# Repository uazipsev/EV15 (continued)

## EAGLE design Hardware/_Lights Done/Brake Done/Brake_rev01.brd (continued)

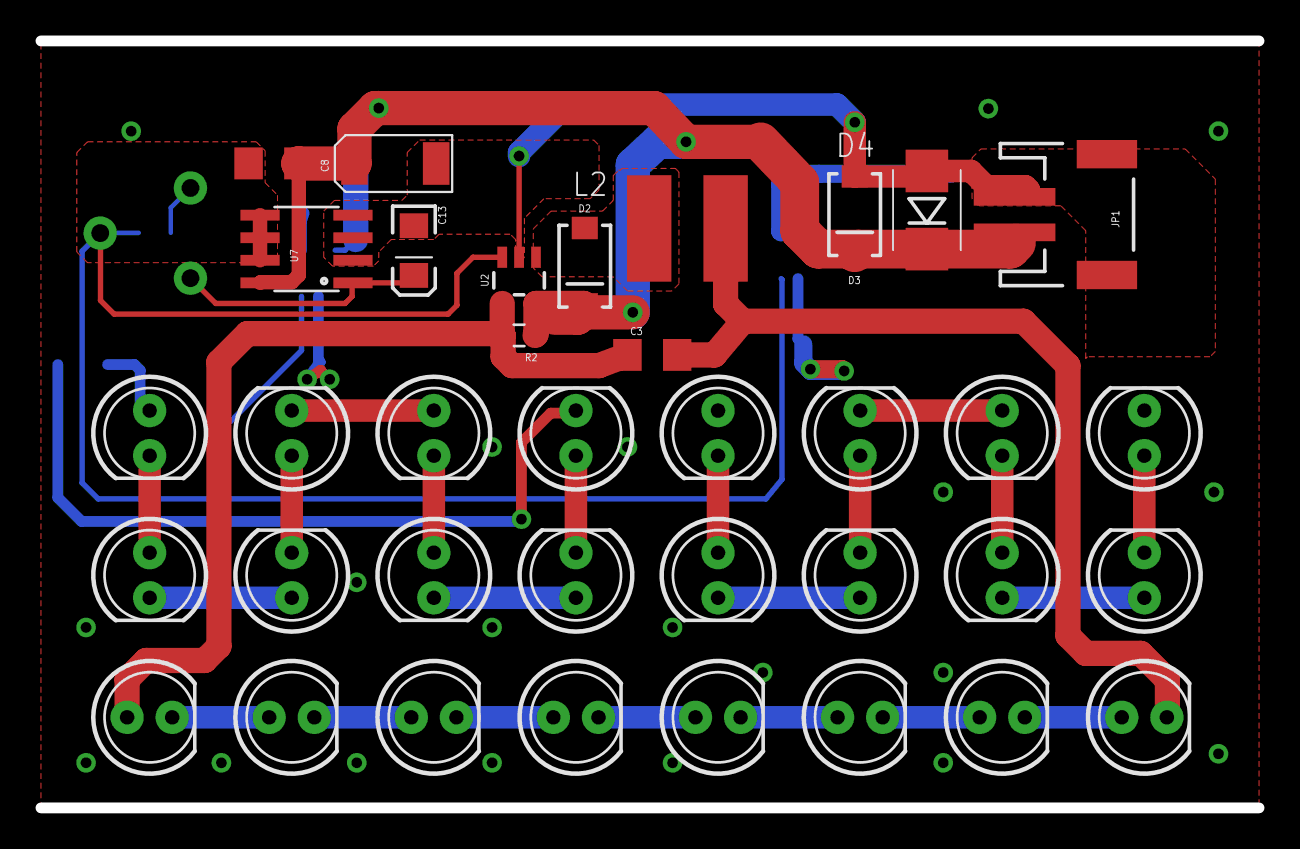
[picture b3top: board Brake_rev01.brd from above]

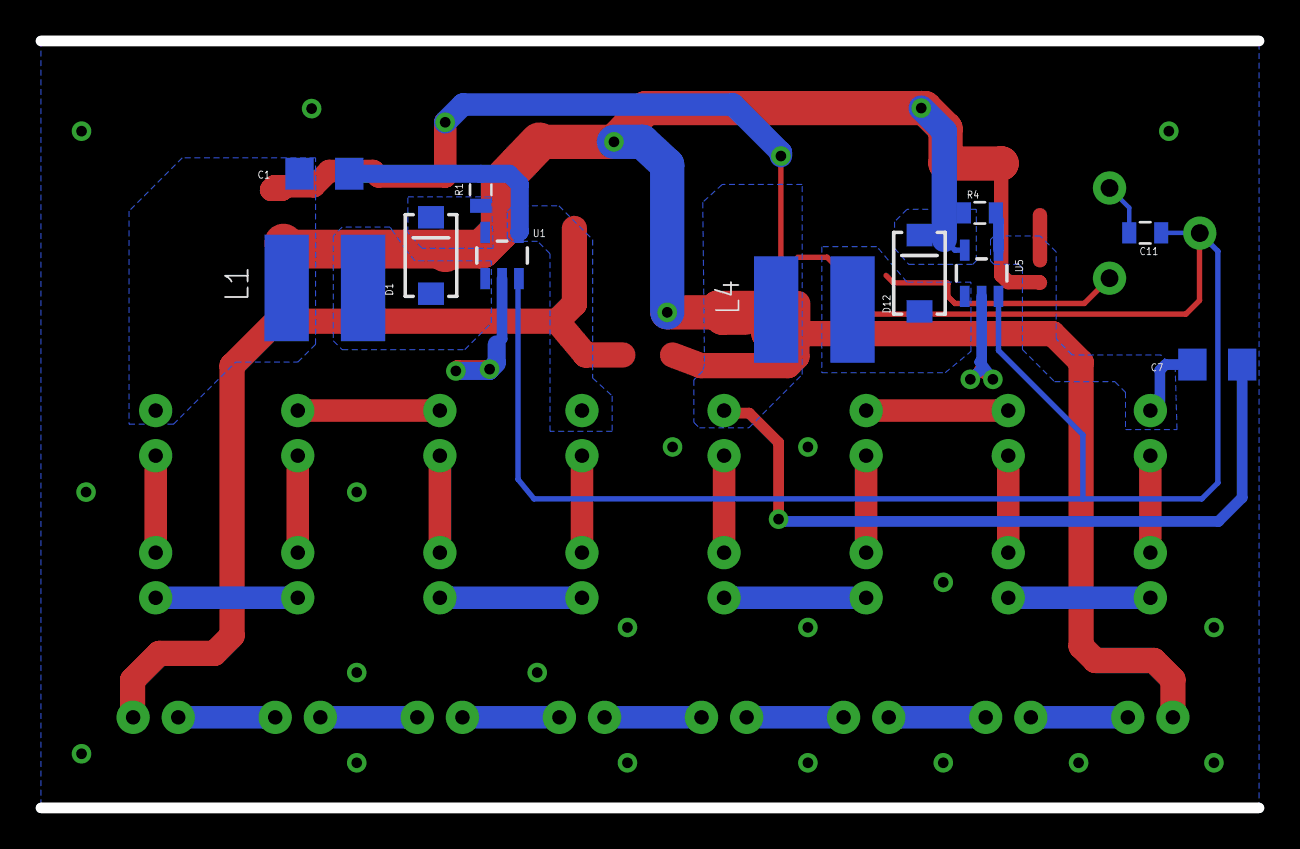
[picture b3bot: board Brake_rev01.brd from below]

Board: 2 copper layers, 68.6 x 43.2 mm, 50 parts (11 on the bottom side), 34 nets.

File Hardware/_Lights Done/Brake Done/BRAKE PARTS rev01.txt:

Partlist

Exported from Brake_rev01.sch at 1/12/15 3:03 PM

EAGLE Version 6.5.0 Copyright (c) 1988-2013 CadSoft

Assembly variant: 

Part     Value           Device                 Package   Library                    Sheet

C1       1uF             1.0UF50V10%(1206)      1206      SparkFun-Capacitors        1
C3       1uF             1.0UF50V10%(1206)      1206      SparkFun-Capacitors        1
C7       1uF             1.0UF50V10%(1206)      1206      SparkFun-Capacitors        1
C8       2.2uF           2.2UF50V10%(1206)      1206      SparkFun-Capacitors        1
C11      10uF            CAP0805                0805      SparkFun-Capacitors        1
C12                      CAP_POL6032            EIA6032   SparkFun-Capacitors        1
C13                      CAP_POL1206            EIA3216   SparkFun-Capacitors        1
D1       MBRA140         DIODE-SCHOTTKY-MBRA140 SMA-DIODE SparkFun-DiscreteSemi      1
D2       MBRA140         DIODE-SCHOTTKY-MBRA140 SMA-DIODE SparkFun-DiscreteSemi      1
D3       TVS             TVS                    SMA-DIODE SparkFun-DiscreteSemi      1
D4       30v             DIODE-ZENERSMB         SMB-DIODE SparkFun-DiscreteSemi      1
D12      MBRA140         DIODE-SCHOTTKY-MBRA140 SMA-DIODE SparkFun-DiscreteSemi      1
JP1      M02-JST-2MM-SMT M02-JST-2MM-SMT        JST-2-SMD SparkFun-Connectors        1
L1       33uH            INDUCTORBOURNS_SRN6045 SRN6045   SparkFun-Passives          1
L2       33uH            INDUCTORBOURNS_SRN6045 SRN6045   SparkFun-Passives          1
L4       33uH            INDUCTORBOURNS_SRN6045 SRN6045   SparkFun-Passives          1
LED1                     LED5MM                 LED5MM    SparkFun-LED               1
LED2                     LED5MM                 LED5MM    SparkFun-LED               1
LED3                     LED5MM                 LED5MM    SparkFun-LED               1
LED4                     LED5MM                 LED5MM    SparkFun-LED               1
LED5                     LED5MM                 LED5MM    SparkFun-LED               1
LED6                     LED5MM                 LED5MM    SparkFun-LED               1
LED7                     LED5MM                 LED5MM    SparkFun-LED               1
LED8                     LED5MM                 LED5MM    SparkFun-LED               1
LED9                     LED5MM                 LED5MM    SparkFun-LED               1
LED10                    LED5MM                 LED5MM    SparkFun-LED               1
LED11                    LED5MM                 LED5MM    SparkFun-LED               1
LED12                    LED5MM                 LED5MM    SparkFun-LED               1
LED13                    LED5MM                 LED5MM    SparkFun-LED               1
LED14                    LED5MM                 LED5MM    SparkFun-LED               1
LED15                    LED5MM                 LED5MM    SparkFun-LED               1
LED16                    LED5MM                 LED5MM    SparkFun-LED               1
LED17                    LED5MM                 LED5MM    SparkFun-LED               1
LED18                    LED5MM                 LED5MM    SparkFun-LED               1
LED19                    LED5MM                 LED5MM    SparkFun-LED               1
LED20                    LED5MM                 LED5MM    SparkFun-LED               1
LED21                    LED5MM                 LED5MM    SparkFun-LED               1
LED22                    LED5MM                 LED5MM    SparkFun-LED               1
LED23                    LED5MM                 LED5MM    SparkFun-LED               1
LED24                    LED5MM                 LED5MM    SparkFun-LED               1
R1       5R              0.3OHM-1/8W-1%(0805)   0805      SparkFun-Resistors         1
R2       5R              0.3OHM-1/8W-1%(0805)   0805      SparkFun-Resistors         1
R4       5R              0.3OHM-1/8W-1%(0805)   0805      SparkFun-Resistors         1
RV1                      POTTRIM                TRIM_POT  SparkFun-Electromechanical 1
U1                       AL8805                 SOT23-5   SparkFun-PowerIC           1
U2                       AL8805                 SOT23-5   SparkFun-PowerIC           1
U5                       AL8805                 SOT23-5   SparkFun-PowerIC           1
U7       LM2931D-5.0R2G  LM2931                 SO08      SparkFun-PowerIC           1

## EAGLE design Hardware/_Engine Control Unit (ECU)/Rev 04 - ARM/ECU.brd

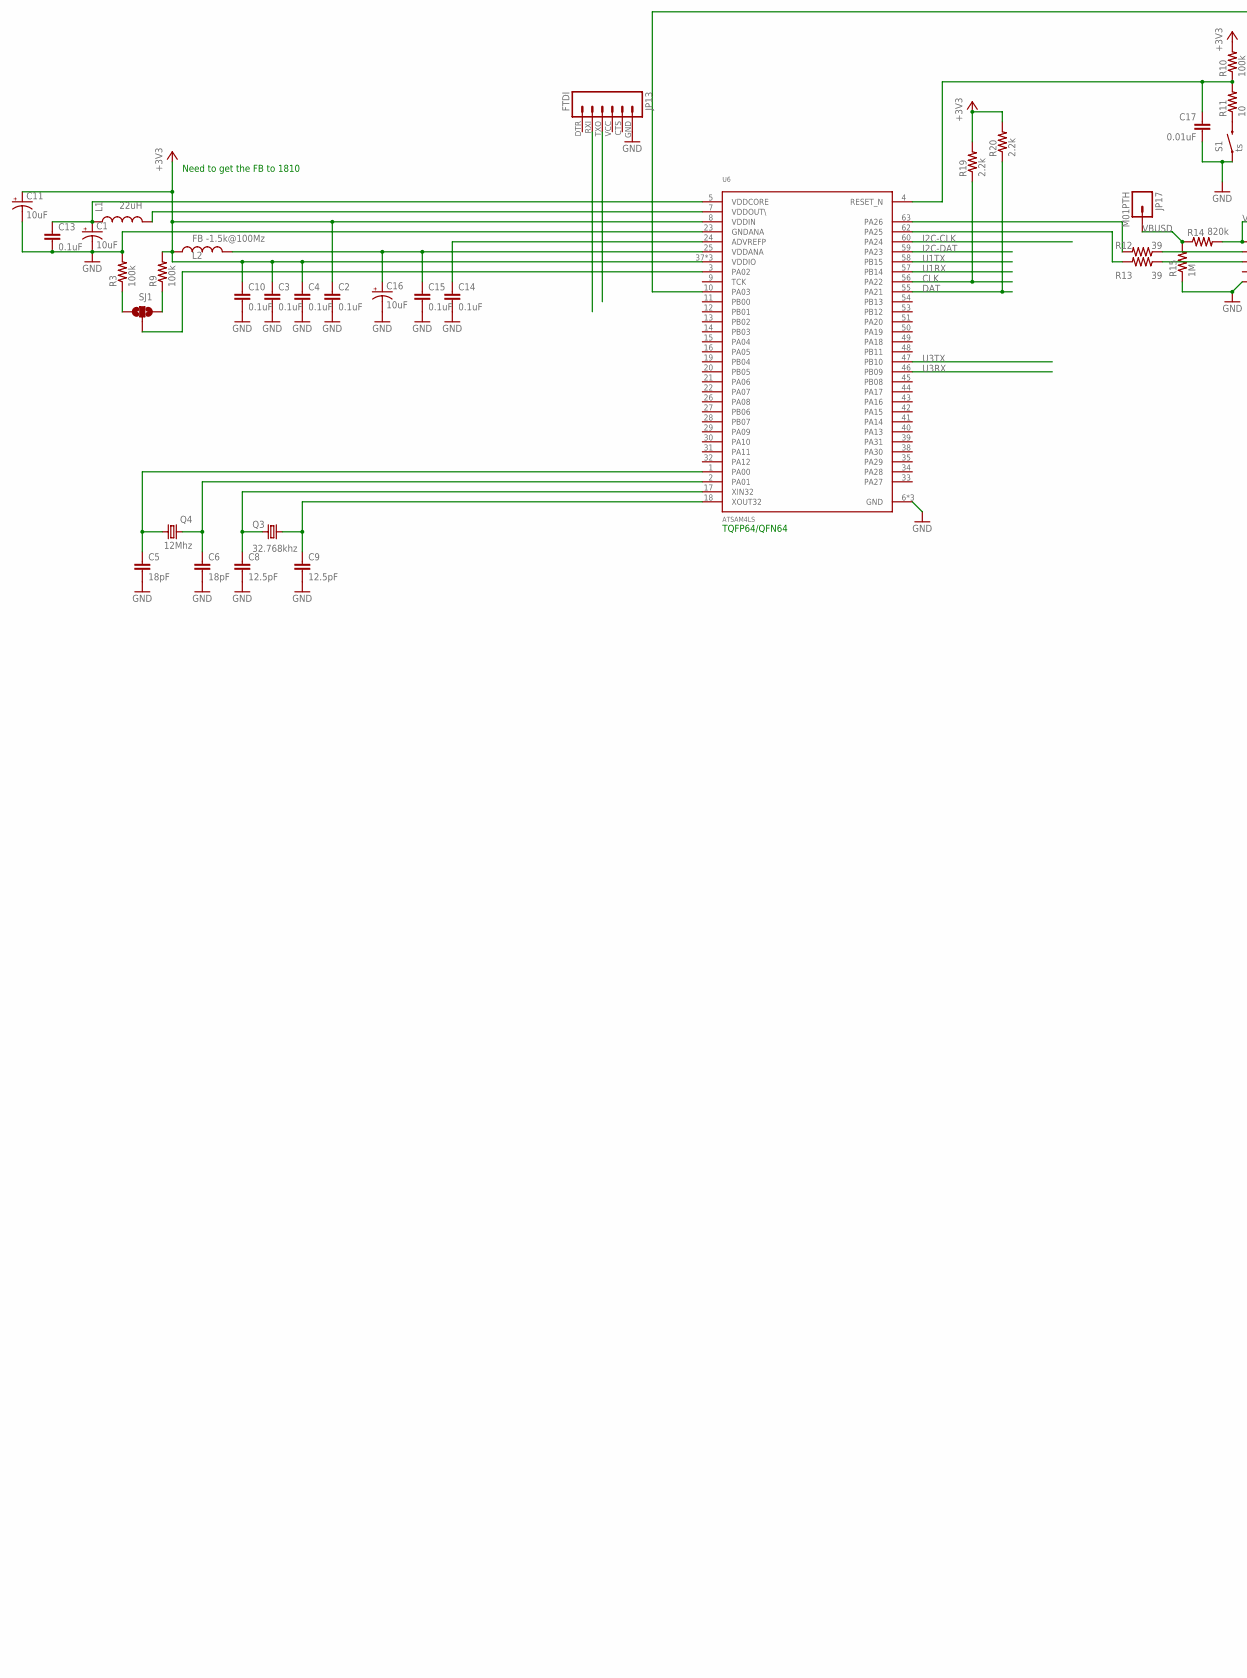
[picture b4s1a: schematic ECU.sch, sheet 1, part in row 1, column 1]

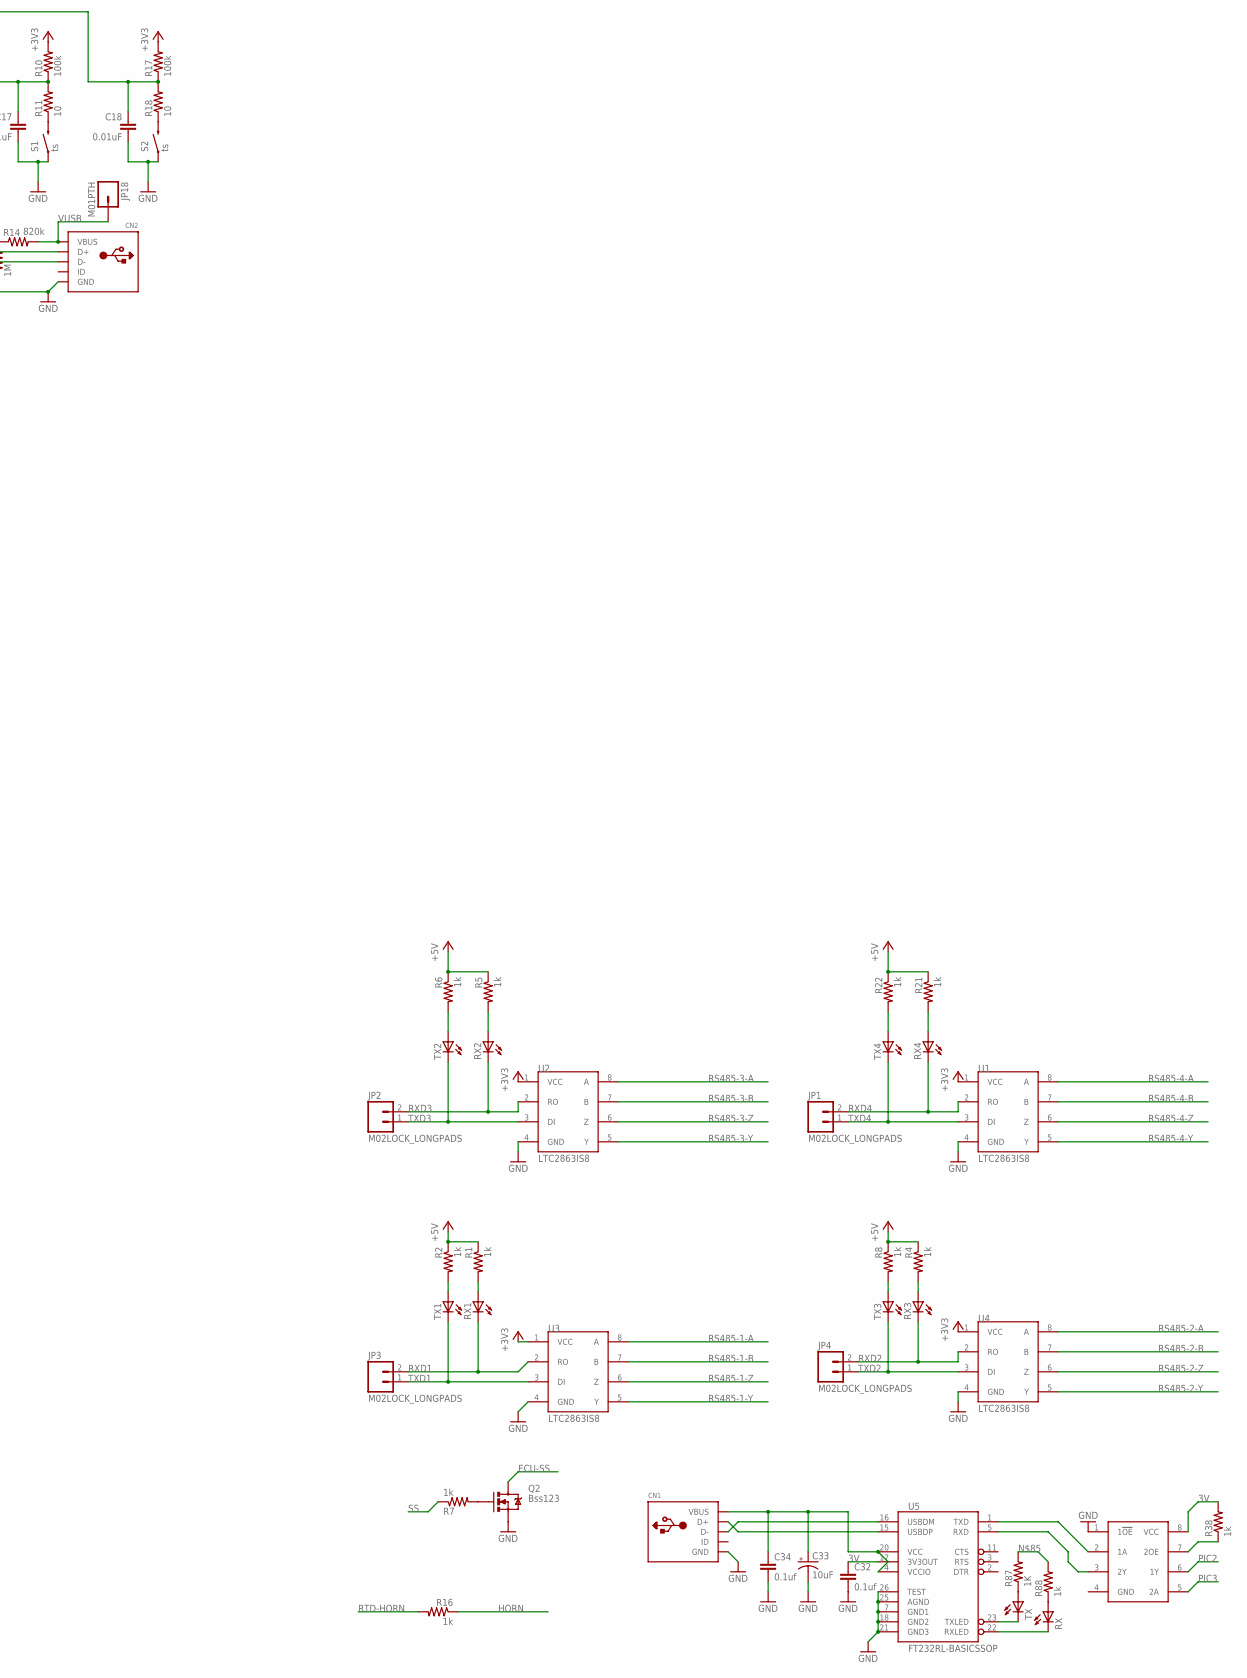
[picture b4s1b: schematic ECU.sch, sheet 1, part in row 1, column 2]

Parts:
C1, C11, C16, C33: 10uF; EIA3216
C2, C3, C4, C10, C13, C14, C15: 0.1uF; 0805
C5, C6: 18pF; 0805
C8, C9: 12.5pF; 0805
C17, C18: 0.01uF; 0805
C32, C34: 0.1uf; 0805
CN1, CN2: USBMOLEX; USB-MINIB-THM-MOLEX
JP1, JP2, JP3, JP4: M02LOCK_LONGPADS; 1X02_LOCK_LONGPADS
JP13: FTDI; FTDI_BASIC
JP17, JP18: M01PTH; 1X01
L1: 22uH; 0805
L2: FB -1.5k@100Mz; 0805
Q2: Bss123; SOT23
Q3: 32.768khz; MM20SS
Q4: 12Mhz; CTS406
R1, R2, R4, R5, R6, R7, R8, R16, R21, R22: 1k; 0805
R3, R9, R10, R17: 100k; 0805
R11, R18: 10; 0805
R12, R13: 39; 0805
R14: 820k; 0805
R15: 1M; 0805
R19, R20: 2.2k; 0805
R38, R88: 1k; R0805
R87: 1K; R0805
RX: LEDCHIPLED_0805; CHIPLED_0805
RX1, RX2, RX3, RX4: LEDCHIP-LED0805; CHIP-LED0805
S1, S2: ts; TACTILE-PTH-SIDEEZ
SJ1: SOLDERJUMPER_2WAYS; SJ_3
TX: LEDCHIPLED_0805; CHIPLED_0805
TX1, TX2, TX3, TX4: LEDCHIP-LED0805; CHIP-LED0805
U1, U2, U3, U4: LTC2863IS8; SO08
U5: FT232RL-BASICSSOP; SSOP28DB
U6: ATSAM4LS; TQFP-64
U14: SN74LVC2G241DCTR; VFSOP-8

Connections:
3V: C32.1, R38.2, U5.17 (3V3OUT), U14.8 (VCC)
+3V3: C2.1, C3.1, C4.1, C10.1, C11.A (+), L2.1, R9.2, R10.2, R17.2, R19.2, R20.2, U1.1 (VCC), U2.1 (VCC), U3.1 (VCC), U4.1 (VCC), U6.8 (VDDIN), U6.37 (VDDIO), U6.52 (VDDIO), U6.61 (VDDIO); also elsewhere on the board
+5V: R1.1, R2.1, R4.1, R5.1, R6.1, R8.1, R21.1, R22.1
CLK: R19.1, U6.56 (PA22)
DAT: R20.1, U6.55 (PA21)
ECU-SS: Q2.3 (D)
GND: C1.C (-), C2.2, C3.2, C4.2, C5.2, C6.2, C8.2, C9.2, C10.2, C11.C (-), C13.2, C14.2, C15.2, C16.C (-), C17.2, C18.2, C32.2, C33.C (-), C34.2, CN1.GND, CN2.GND, JP13.GND (6), Q2.2 (S), R3.2, R15.1, S1.1, S2.1, U1.4 (GND), U2.4 (GND), U3.4 (GND), U4.4 (GND), U5.7 (GND1), U5.18 (GND2), U5.21 (GND3), U5.25 (AGND), U5.26 (TEST), U6.6 (GND), U6.23 (GNDANA), U6.36 (GND), U6.64 (GND), U14.1 (1!OE); also elsewhere on the board
HORN: R16.1
I2C-CLK: U6.60 (PA24)
I2C-DAT: U6.59 (PA23)
unnamed: R11.1, S1.2
unnamed: L1.2, U6.7 (VDDOUT\)
unnamed: R38.1, U14.7 (2OE)
unnamed: C1.A (+), C13.1, L1.1, U6.5 (VDDCORE)
unnamed: C8.1, Q3.1, U6.17 (XIN32)
unnamed: R1.2, RX1.A
unnamed: R2.2, TX1.A
unnamed: C9.1, Q3.4 (2), U6.18 (XOUT32)
unnamed: C6.1, Q4.1, U6.2 (PA01)
unnamed: C5.1, Q4.3 (2), U6.1 (PA00)
unnamed: R4.2, RX3.A
unnamed: R8.2, TX3.A
unnamed: R3.1, SJ1.3
unnamed: R9.1, SJ1.1
unnamed: C15.1, C16.A (+), L2.2, U6.25 (VDDANA)
unnamed: R5.2, RX2.A
unnamed: R6.2, TX2.A
unnamed: SJ1.2, U6.3 (PA02)
unnamed: C14.1, U6.24 (ADVREFP)
unnamed: C17.1, R10.1, R11.2, U6.4 (RESET_N)
unnamed: CN2.D+, R12.1
unnamed: R21.2, RX4.A
unnamed: CN2.D-, R13.1
unnamed: R18.1, S2.2
unnamed: C18.1, R17.1, R18.2, U6.10 (PA03)
unnamed: Q2.1 (G), R7.2
unnamed: R12.2, U6.63 (PA26)
unnamed: R13.2, U6.62 (PA25)
unnamed: R22.2, TX4.A
unnamed: CN1.D-, U5.16 (USBDM)
unnamed: CN1.D+, U5.15 (USBDP)
unnamed: R87.1, TX.A
unnamed: R88.1, RX.A
unnamed: TX.C, U5.23 (TXLED)
unnamed: RX.C, U5.22 (RXLED)
unnamed: C33.A (+), C34.1, CN1.VBUS, R87.2, R88.2, U5.4 (VCCIO), U5.20 (VCC)
unnamed: U5.1 (TXD), U14.2 (1A)
unnamed: U5.5 (RXD), U14.3 (2Y)
PIC2: U14.6 (1Y)
PIC3: U14.5 (2A)
RS485-1-A: U3.8 (A); also elsewhere on the board
RS485-1-B: U3.7 (B); also elsewhere on the board
RS485-1-Y: U3.5 (Y); also elsewhere on the board
RS485-1-Z: U3.6 (Z); also elsewhere on the board
RS485-2-A: U4.8 (A); also elsewhere on the board
RS485-2-B: U4.7 (B); also elsewhere on the board
RS485-2-Y: U4.5 (Y); also elsewhere on the board
RS485-2-Z: U4.6 (Z); also elsewhere on the board
RS485-3-A: U2.8 (A); also elsewhere on the board
RS485-3-B: U2.7 (B); also elsewhere on the board
RS485-3-Y: U2.5 (Y); also elsewhere on the board
RS485-3-Z: U2.6 (Z); also elsewhere on the board
RS485-4-A: U1.8 (A); also elsewhere on the board
RS485-4-B: U1.7 (B); also elsewhere on the board
RS485-4-Y: U1.5 (Y); also elsewhere on the board
RS485-4-Z: U1.6 (Z); also elsewhere on the board
RTD-HORN: R16.2
RXD1: JP3.2, RX1.C, U3.2 (RO)
RXD2: JP4.2, RX3.C, U4.2 (RO)
RXD3: JP2.2, RX2.C, U2.2 (RO)
RXD4: JP1.2, RX4.C, U1.2 (RO)
SS: R7.1
TXD1: JP3.1, TX1.C, U3.3 (DI)
TXD2: JP4.1, TX3.C, U4.3 (DI)
TXD3: JP2.1, TX2.C, U2.3 (DI)
TXD4: JP1.1, TX4.C, U1.3 (DI)
U0RX: JP13.TXO (3)
U0TX: JP13.RXI (2)
U1RX: U6.57 (PB14)
U1TX: U6.58 (PB15)
U3RX: U6.46 (PB09)
U3TX: U6.47 (PB10)
VBUSD: JP17.1, R14.1, R15.2
VUSB: CN2.VBUS, JP18.1, R14.2

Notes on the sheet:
TQFP64/QFN64
Need to get the FB to 1810

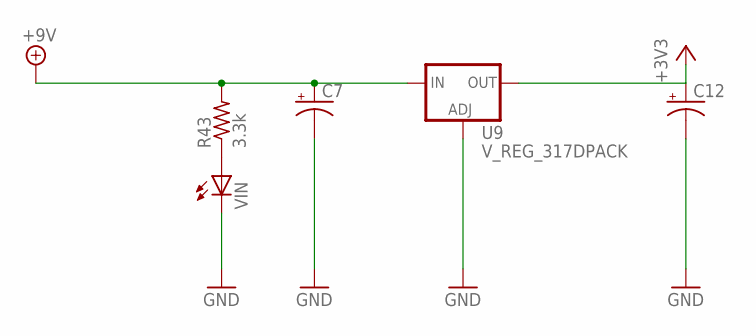
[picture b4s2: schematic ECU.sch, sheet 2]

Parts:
C7: CAP_POL7343; EIA7343
C12: CAP_POL3528; EIA3528
R43: 3.3k; R0805
U9: V_REG_317DPACK; V-REG_DPACK
VIN: LEDCHIP-LED0805; CHIP-LED0805

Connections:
+3V3: C12.A (+), U9.4 (OUT); also elsewhere on the board
+9V: C7.A (+), R43.2, U9.3 (IN); also elsewhere on the board
GND: C7.C (-), C12.C (-), U9.1 (ADJ), VIN.C; also elsewhere on the board
unnamed: R43.1, VIN.A

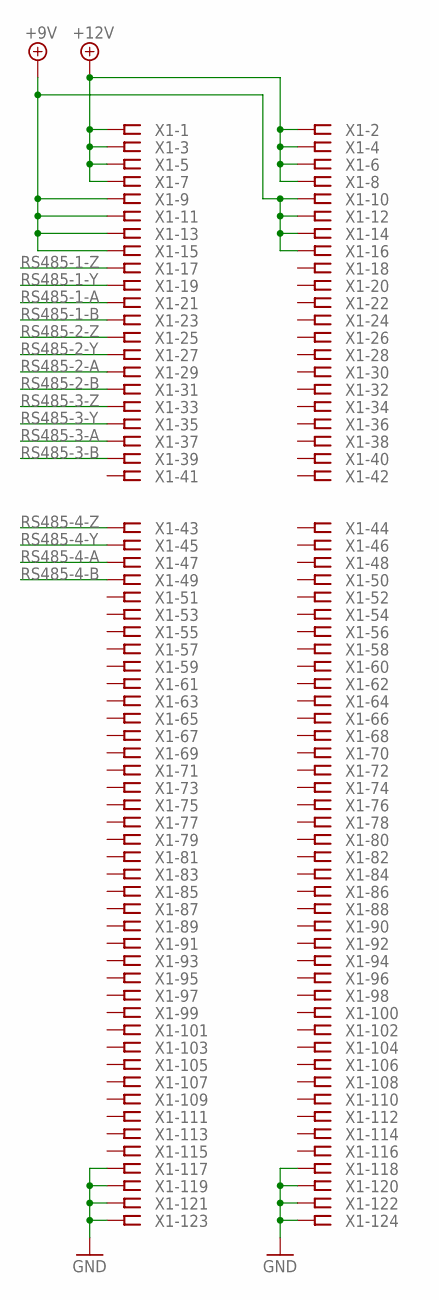
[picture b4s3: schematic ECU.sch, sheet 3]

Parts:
X1: AGP-3X3

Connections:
+9V: X1.9, X1.10, X1.11, X1.12, X1.13, X1.14, X1.15, X1.16; also elsewhere on the board
+12V: X1.1, X1.2, X1.3, X1.4, X1.5, X1.6, X1.7, X1.8
GND: X1.117, X1.118, X1.119, X1.120, X1.121, X1.122, X1.123, X1.124; also elsewhere on the board
RS485-1-A: X1.21; also elsewhere on the board
RS485-1-B: X1.23; also elsewhere on the board
RS485-1-Y: X1.19; also elsewhere on the board
RS485-1-Z: X1.17; also elsewhere on the board
RS485-2-A: X1.29; also elsewhere on the board
RS485-2-B: X1.31; also elsewhere on the board
RS485-2-Y: X1.27; also elsewhere on the board
RS485-2-Z: X1.25; also elsewhere on the board
RS485-3-A: X1.37; also elsewhere on the board
RS485-3-B: X1.39; also elsewhere on the board
RS485-3-Y: X1.35; also elsewhere on the board
RS485-3-Z: X1.33; also elsewhere on the board
RS485-4-A: X1.47; also elsewhere on the board
RS485-4-B: X1.49; also elsewhere on the board
RS485-4-Y: X1.45; also elsewhere on the board
RS485-4-Z: X1.43; also elsewhere on the board

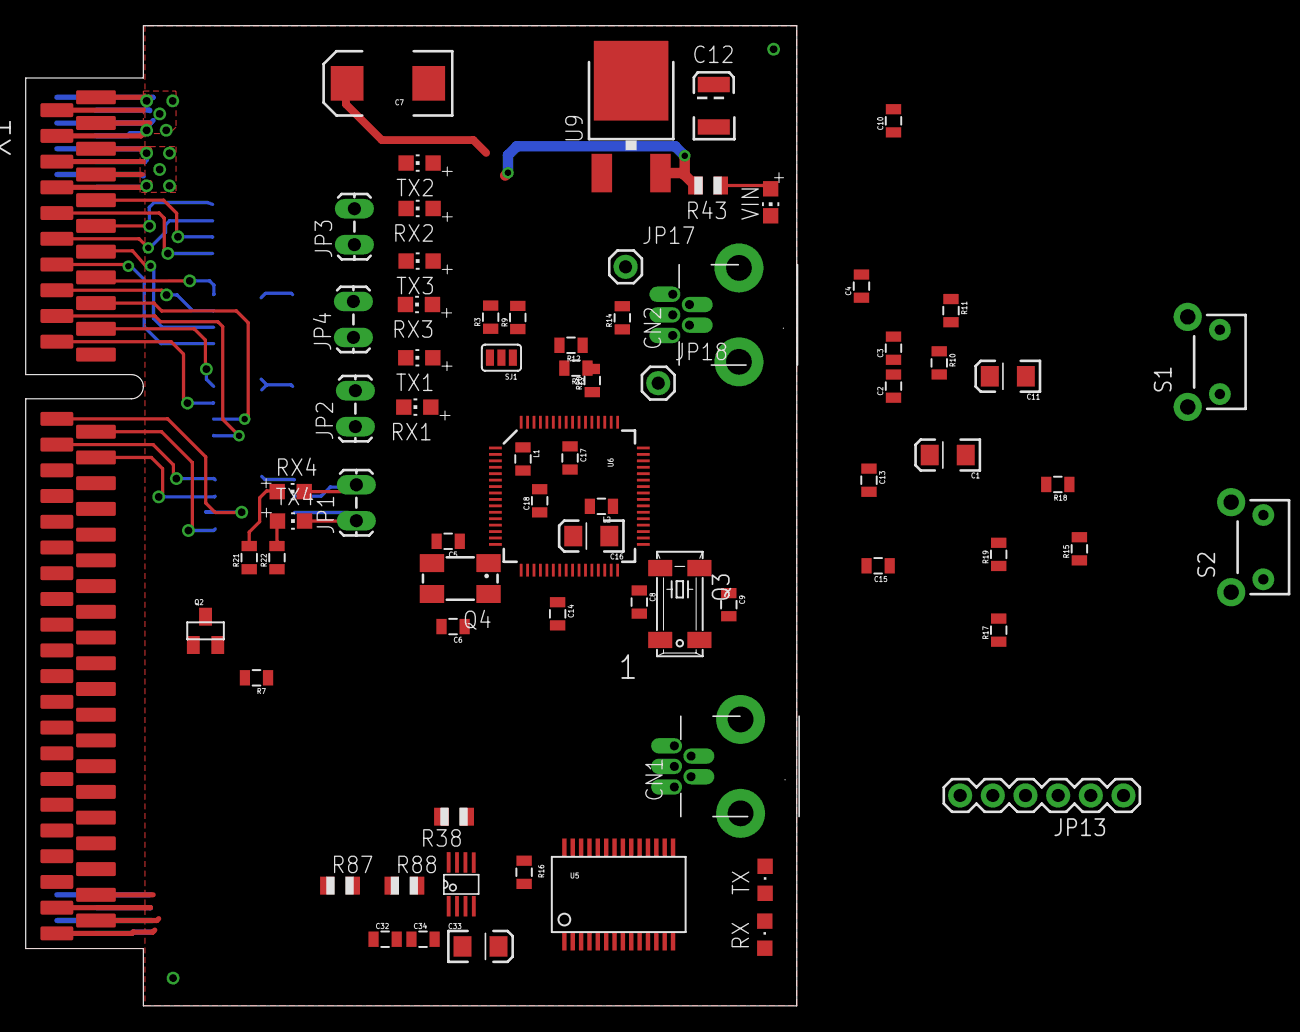
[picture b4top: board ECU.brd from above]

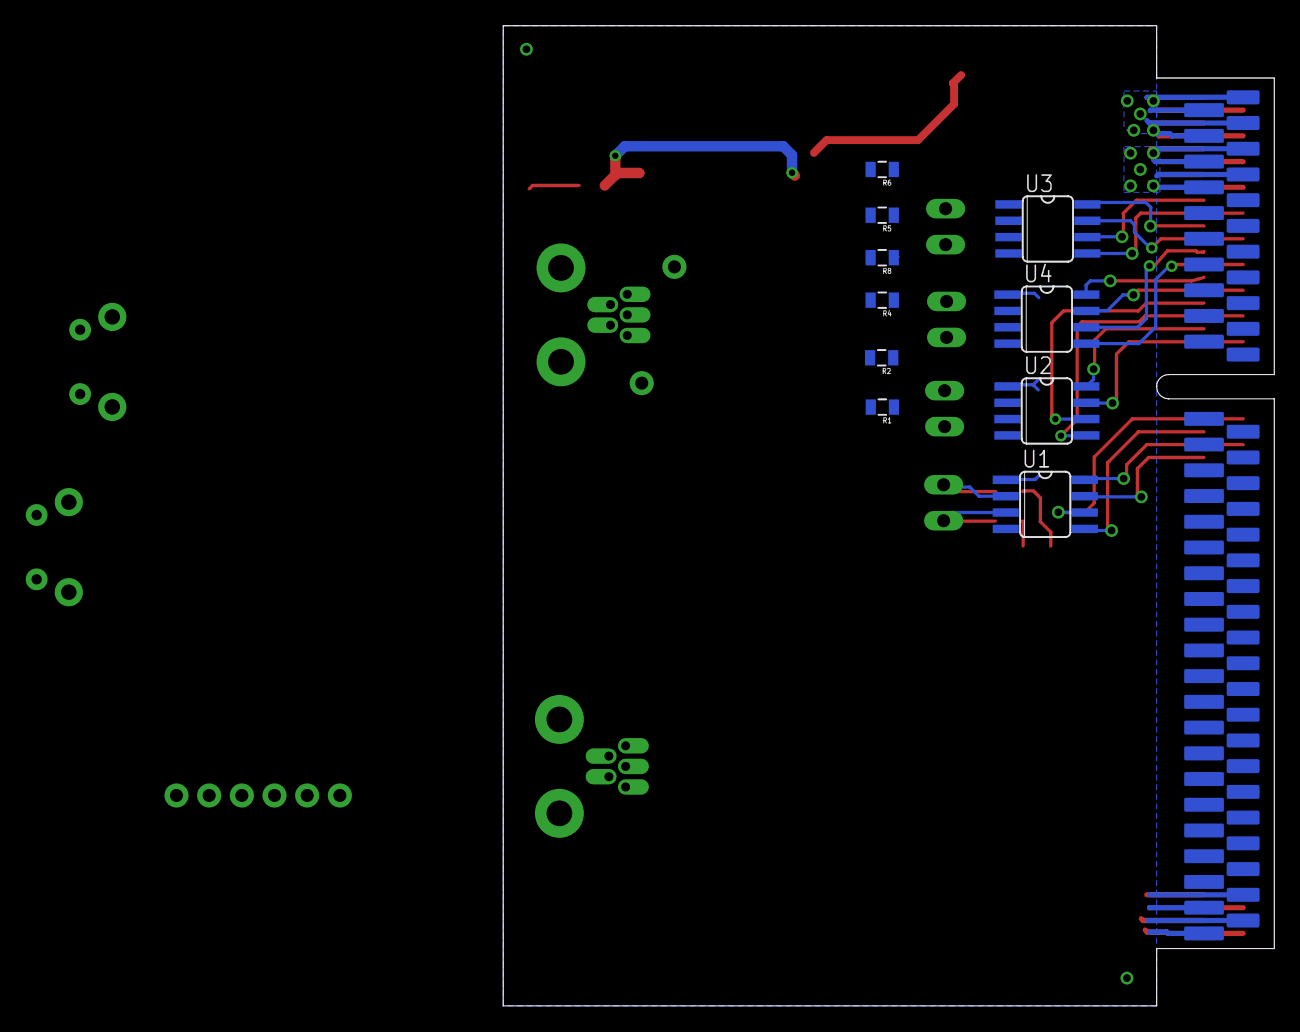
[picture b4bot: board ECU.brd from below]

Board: 2 copper layers, 59.9 x 76.2 mm, 84 parts (10 on the bottom side), 73 nets.

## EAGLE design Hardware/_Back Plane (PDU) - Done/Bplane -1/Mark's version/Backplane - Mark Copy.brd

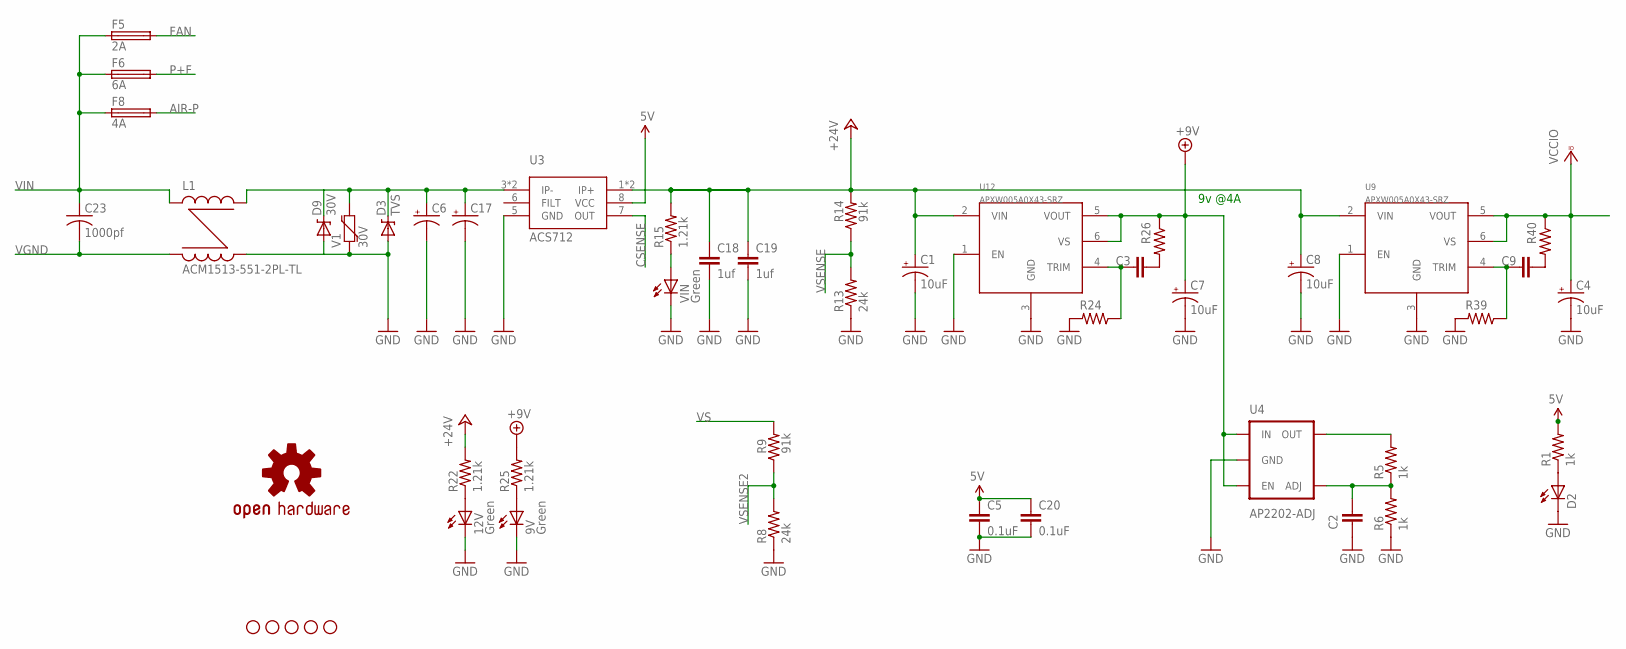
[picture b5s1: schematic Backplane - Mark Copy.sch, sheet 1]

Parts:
9V, 12V: Green; CHIP-LED0805
C1, C4, C7, C8: 10uF; EIA3528
C2, C3, C9: CAP0805; 0805
C5, C20: 0.1uF; 0805
C6, C17: CPOL-USG; PANASONIC_G
C18, C19: 1uf; 1206
C23: 1000pf; C1825
D2: LEDCHIP-LED0805; CHIP-LED0805
D3: TVS; DO-214AC
D9: 30V; SMB-DIODE
F5: 2A; F456
F6: 6A; F456
F8: 4A; F456
L1: ACM1513-551-2PL-TL
R1, R5, R6: 1k; R0805
R8, R13: 24k; R0805
R9, R14: 91k; R0805
R15, R22, R25: 1.21k; R0805
R24, R26, R39, R40: R-US_R0805; R0805
STANDOFF1, STANDOFF2, STANDOFF3, STANDOFF4, STANDOFF5: STAND-OFF
U3: ACS712; SO-8
U4: AP2202-ADJ; SOT23-5
U9, U12: APXW005A0X43-SRZ
U$8: OSHW-LOGOM; OSHW-LOGO-M
V1: 30V; 0603-RES
VIN: Green; CHIP-LED0805

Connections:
5V: C5.1, C20.1, R1.2, U3.8 (VCC); also elsewhere on the board
+9V: C7.A (+), R25.2, R26.1, U4.1 (IN), U4.3 (EN), U12.5 (VOUT), U12.6 (VS)
+24V: C1.A (+), C8.A (+), C18.1, C19.1, R14.2, R15.2, R22.2, U3.1 (IP+), U3.2 (IP+), U9.2 (VIN), U12.2 (VIN); also elsewhere on the board
AIR-P: F8.2; also elsewhere on the board
CSENSE: U3.7 (OUT); also elsewhere on the board
FAN: F5.2; also elsewhere on the board
GND: 9V.C, 12V.C, C1.C (-), C2.2, C4.C (-), C5.2, C6.-, C7.C (-), C8.C (-), C17.-, C18.2, C19.2, C20.2, D2.C, D3.A, D9.A, L1.OUT-, R6.1, R8.1, R13.1, R24.2, R39.2, U3.5 (GND), U4.2 (GND), U9.1 (EN), U9.3 (GND), U12.1 (EN), U12.3 (GND), V1.1, VIN.C; also elsewhere on the board
unnamed: C2.1, R5.1, R6.2, U4.4 (ADJ)
unnamed: R5.2, U4.5 (OUT)
unnamed: 9V.A, R25.1
unnamed: D2.A, R1.1
unnamed: 12V.A, R22.1
unnamed: C6.+, C17.+, D3.C, D9.C, L1.OUT+, U3.3 (IP-), U3.4 (IP-), V1.2
unnamed: C3.1, R26.2
unnamed: C3.2, R24.1, U12.4 (TRIM)
unnamed: R15.1, VIN.A
unnamed: C9.1, R40.2
unnamed: C9.2, R39.1, U9.4 (TRIM)
P+F: F6.2; also elsewhere on the board
VCCIO: C4.A (+), R40.1, U9.5 (VOUT), U9.6 (VS); also elsewhere on the board
VGND: C23.2, L1.IN-; also elsewhere on the board
VIN: C23.1, F5.1, F6.1, F8.1, L1.IN+; also elsewhere on the board
VS: R9.2
VSENSE: R13.2, R14.1; also elsewhere on the board
VSENSE2: R8.2, R9.1

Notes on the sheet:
9v @4A

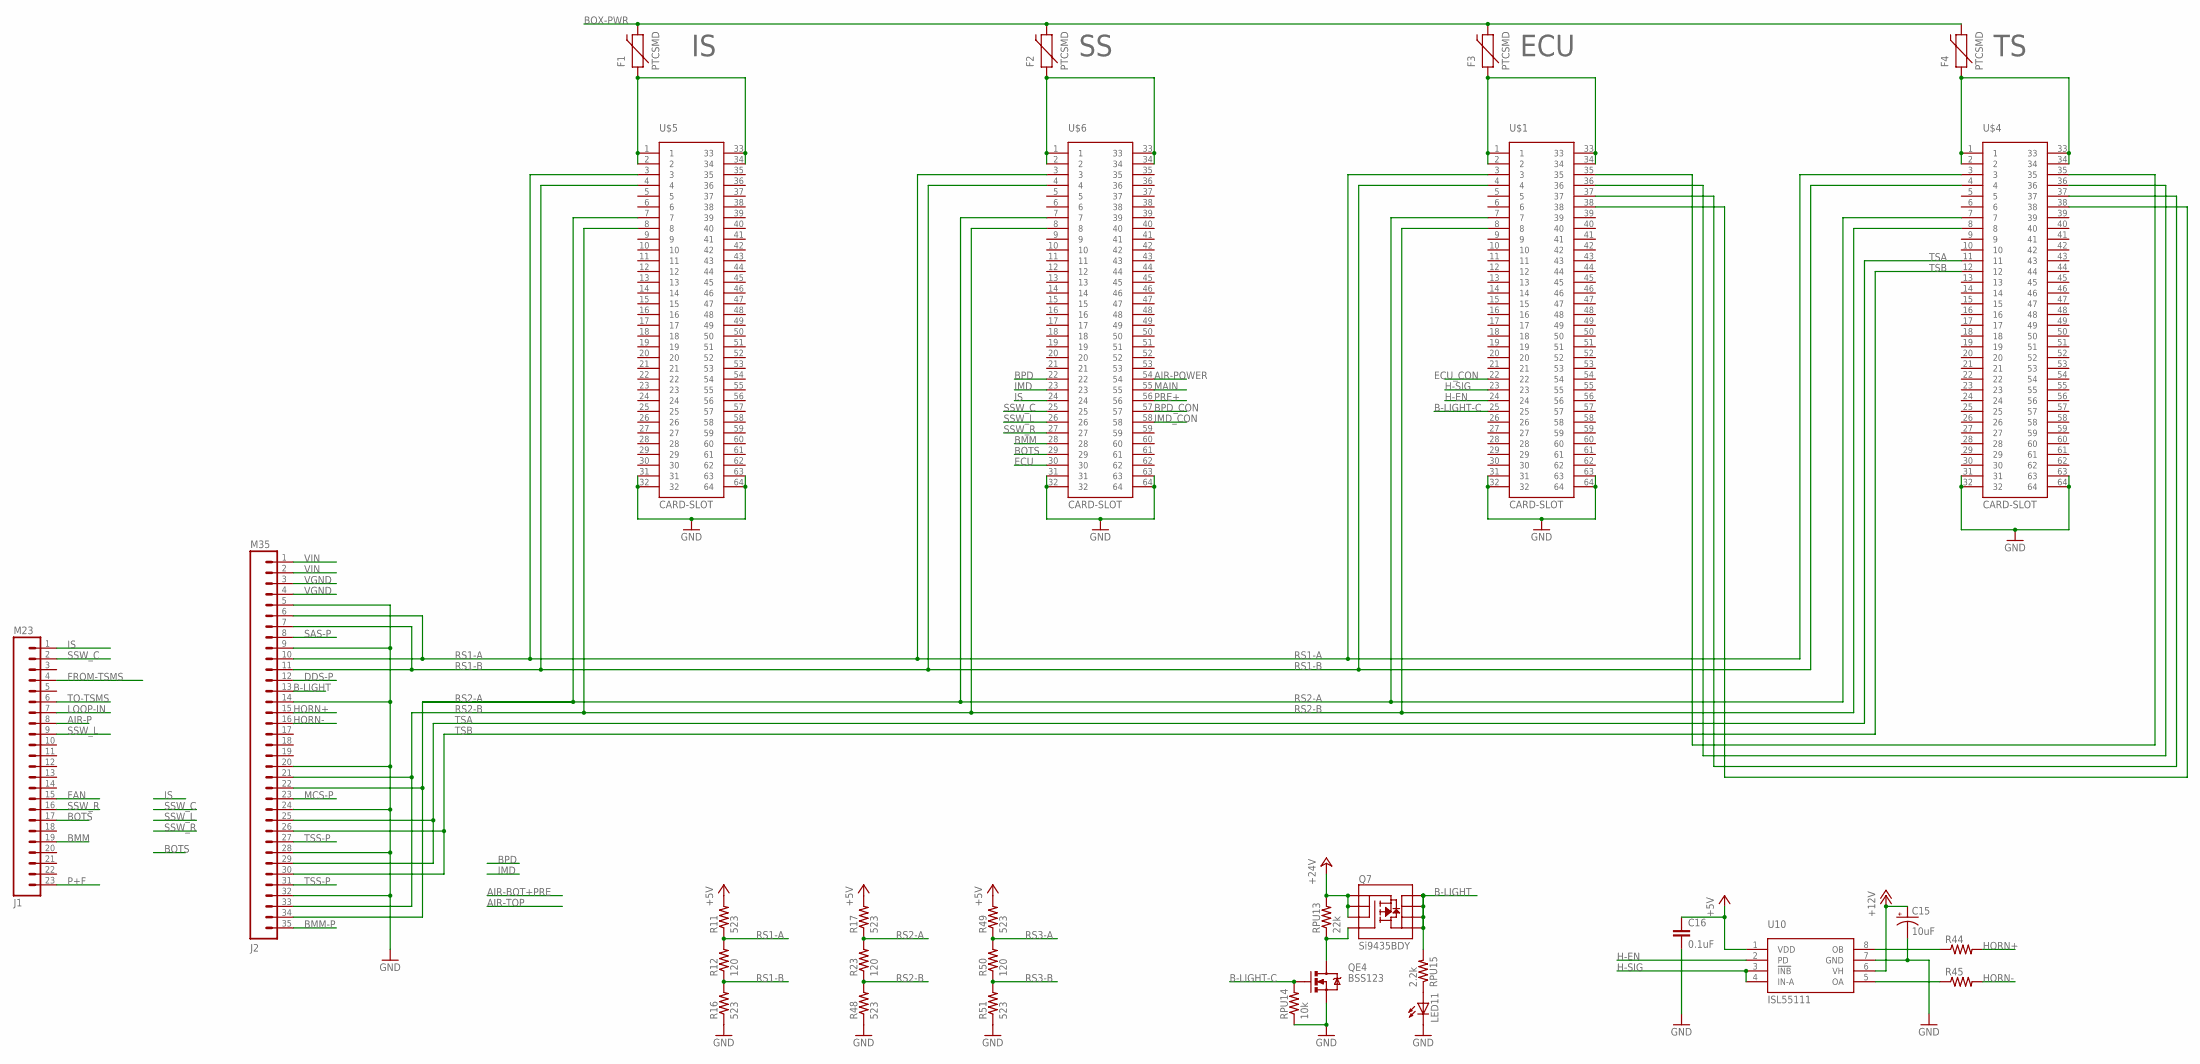
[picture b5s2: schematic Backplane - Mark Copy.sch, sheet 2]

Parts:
C15: 10uF; EIA3528
C16: 0.1uF; 0805
F1, F2, F3, F4: PTCSMD; PTC-1206
J1: M23; 1-770669-1
J2: M35; 1-776163-2
LED11: LEDCHIP-LED0805; CHIP-LED0805
Q7: Si9435BDY; SO08
QE4: BSS123; SOT-23
R11, R16, R17, R48, R49, R51: 523; 0805
R12, R23, R50: 120; 0805
R44, R45: RESISTOR0805-RES; 0805
RPU13: 22k; 0805
RPU14: 10k; 0805
RPU15: 2.2k; 0805
U10: ISL55111; TSSOP-8
U$1, U$4, U$5, U$6: CARD-SLOT; CS64

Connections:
+5V: C16.1, R11.2, R17.2, R49.2, U10.1 (VDD); also elsewhere on the board
+12V: C15.A (+), U10.6 (VH)
+24V: Q7.1 (S), Q7.2 (S), Q7.3 (S), RPU13.2; also elsewhere on the board
AIR-P: J1.8; also elsewhere on the board
AIR-POWER: U$6.54
B-LIGHT: J2.13, Q7.5 (D), Q7.6 (D), Q7.7 (D), Q7.8 (D), RPU15.2
B-LIGHT-C: QE4.1 (G), RPU14.2, U$1.25
BMM: J1.19, U$6.28
BMM-P: J2.35; also elsewhere on the board
BOTS: J1.17, U$6.29
BOX-PWR: F1.2, F2.2, F3.2, F4.2; also elsewhere on the board
BPD: U$6.22; also elsewhere on the board
BPD_CON: U$6.57
DDS-P: J2.12; also elsewhere on the board
ECU: U$6.30; also elsewhere on the board
ECU_CON: U$1.22
FAN: J1.15; also elsewhere on the board
FROM-TSMS: J1.4; also elsewhere on the board
GND: C15.C (-), C16.2, J2.5, J2.9, J2.14, J2.20, J2.24, J2.28, J2.32, LED11.C, QE4.2 (S), R16.1, R48.1, R51.1, RPU14.1, U10.7 (GND), U$1.31, U$1.32, U$1.63, U$1.64, U$4.31, U$4.32, U$4.63, U$4.64, U$5.31, U$5.32, U$5.63, U$5.64, U$6.31, U$6.32, U$6.63, U$6.64; also elsewhere on the board
H-EN: U10.2 (PD), U$1.24
H-SIG: U10.3 (!INB), U10.4 (IN-A), U$1.23
HORN+: J2.15, R44.2
HORN-: J2.16, R45.2
IMD: U$6.23; also elsewhere on the board
IMD_CON: U$6.58
IS: J1.1, U$6.24
LOOP-IN: J1.7; also elsewhere on the board
MAIN: U$6.55; also elsewhere on the board
MCS-P: J2.23; also elsewhere on the board
unnamed: F1.1, U$5.1, U$5.2, U$5.33, U$5.34
unnamed: F2.1, U$6.1, U$6.2, U$6.33, U$6.34
unnamed: F3.1, U$1.1, U$1.2, U$1.33, U$1.34
unnamed: F4.1, U$4.1, U$4.2, U$4.33, U$4.34
unnamed: Q7.4 (G), QE4.3 (D), RPU13.1
unnamed: LED11.A, RPU15.1
unnamed: U$1.38, U$4.38
unnamed: R44.1, U10.8 (OB)
unnamed: R45.1, U10.5 (OA)
unnamed: U$1.37, U$4.37
P+F: J1.23; also elsewhere on the board
PRE+: U$6.56; also elsewhere on the board
RS1-A: J2.6, J2.10, R11.1, R12.2, U$1.3, U$4.3, U$5.3, U$6.3
RS1-B: J2.7, J2.11, R12.1, R16.2, U$1.4, U$4.4, U$5.4, U$6.4
RS2-A: J2.22, J2.34, R17.1, R23.2, U$1.7, U$4.7, U$5.7, U$6.7; also elsewhere on the board
RS2-B: J2.21, J2.33, R23.1, R48.2, U$1.8, U$4.8, U$5.8, U$6.8; also elsewhere on the board
RS3-A: R49.1, R50.2, U$1.35, U$4.35
RS3-B: R50.1, R51.2, U$1.36, U$4.36
SAS-P: J2.8; also elsewhere on the board
SSW_C: J1.2, U$6.25
SSW_L: J1.9, U$6.26
SSW_R: J1.16, U$6.27
TO-TSMS: J1.6; also elsewhere on the board
TSA: J2.25, J2.29, U$4.11
TSB: J2.26, J2.30, U$4.12
TSS-P: J2.27, J2.31; also elsewhere on the board
VGND: J2.3, J2.4; also elsewhere on the board
VIN: J2.1, J2.2; also elsewhere on the board

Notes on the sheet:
ECU
